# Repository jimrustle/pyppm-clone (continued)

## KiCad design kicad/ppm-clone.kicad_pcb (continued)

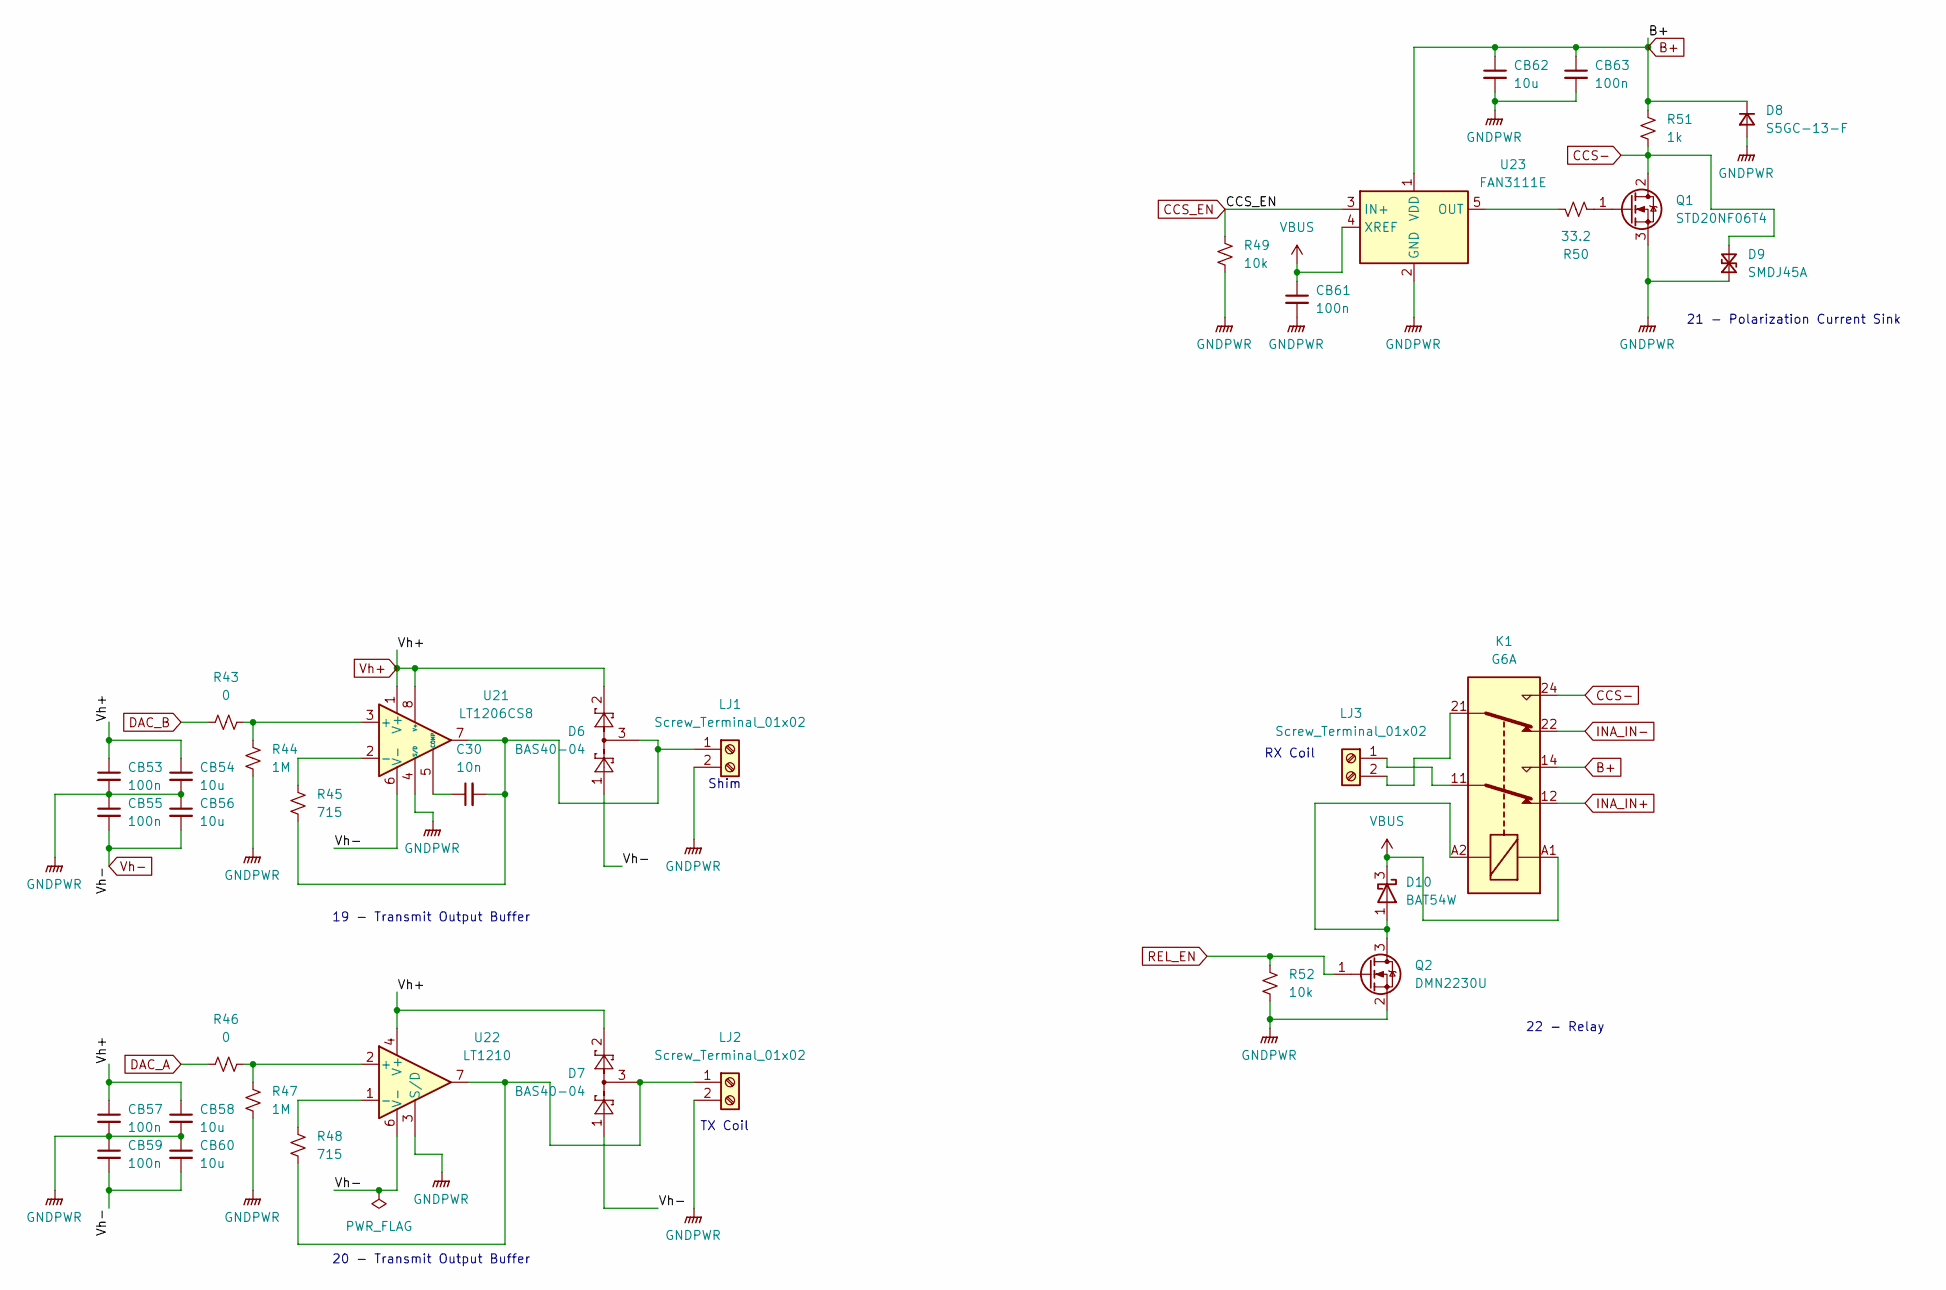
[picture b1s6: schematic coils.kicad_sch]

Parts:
C30: 10n; C_0603_1608Metric_Pad1.08x0.95mm_HandSolder
CB53, CB55, CB57, CB59, CB61, CB63: 100n; C_0603_1608Metric_Pad1.08x0.95mm_HandSolder
CB54, CB56, CB58, CB60, CB62: 10u; C_0603_1608Metric_Pad1.08x0.95mm_HandSolder
D6, D7: BAS40-04; SOT-23
D8: S5GC-13-F; D_SMC-RM10_Universal_Handsoldering
D9: SMDJ45A; D_SMC-RM10_Universal_Handsoldering
D10: BAT54W; SOT-323_SC-70
K1: G6A; Relay_DPDT_Omron_G6A
LJ1, LJ2, LJ3: Screw_Terminal_01x02; TerminalBlock_bornier-2_P5.08mm
Q1: STD20NF06T4; TO-252-2
Q2: DMN2230U; SOT-23
R43, R46: 0; R_0603_1608Metric_Pad0.98x0.95mm_HandSolder
R44, R47: 1M; R_0603_1608Metric_Pad0.98x0.95mm_HandSolder
R45, R48: 715; R_0603_1608Metric_Pad0.98x0.95mm_HandSolder
R49, R52: 10k; R_0603_1608Metric_Pad0.98x0.95mm_HandSolder
R50: 33.2; R_0603_1608Metric_Pad0.98x0.95mm_HandSolder
R51: 1k; R_0603_1608Metric_Pad0.98x0.95mm_HandSolder
U21: LT1206CS8; SO-8_3.9x4.9mm_P1.27mm
U22: LT1210; TO-263-7_TabPin4
U23: FAN3111E; SOT-23-5

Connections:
B+: CB62.1, CB63.1, D8.1 (K), K1.14, R51.1, U23.1 (VDD); also elsewhere on the board
CCS-: D9.2 (A2), K1.24, Q1.2 (D), R51.2
CCS_EN: R49.1, U23.3 (IN+); also elsewhere on the board
DAC_A: R46.1; also elsewhere on the board
DAC_B: R43.1; also elsewhere on the board
GNDPWR: CB53.2, CB54.2, CB55.1, CB56.1, CB57.2, CB58.2, CB59.1, CB60.1, CB61.2, CB62.2, CB63.2, D8.2 (A), D9.1 (A1), LJ1.2, LJ2.2, Q1.3 (S), Q2.2 (S), R44.2, R47.2, R49.2, R52.2, U21.4 (S/D), U22.3 (S/D), U23.2 (GND); also elsewhere on the board
INA_IN+: K1.12; also elsewhere on the board
INA_IN-: K1.22; also elsewhere on the board
unnamed: D10.1 (A), K1.A2, Q2.3 (D)
unnamed: C30.2, D6.3, LJ1.1, R45.2, U21.7
unnamed: D7.3, LJ2.1, R48.2, U22.7
unnamed: K1.11, LJ3.1
unnamed: K1.21, LJ3.2
unnamed: Q1.1 (G), R50.2
unnamed: R43.2, R44.1, U21.3 (+)
unnamed: R45.1, U21.2 (-)
unnamed: C30.1, U21.5 (COMP)
unnamed: R46.2, R47.1, U22.2 (+)
unnamed: R48.1, U22.1 (-)
unnamed: R50.1, U23.5 (OUT)
REL_EN: Q2.1 (G), R52.1; also elsewhere on the board
VBUS: CB61.1, D10.3 (K), K1.A1, U23.4 (XREF); also elsewhere on the board
Vh+: CB53.1, CB54.1, CB57.1, CB58.1, D6.2, D7.2, U21.1 (V+), U21.8 (V+), U22.4 (V+); also elsewhere on the board
Vh-: CB55.2, CB56.2, CB59.2, CB60.2, D6.1, D7.1, U21.6 (V-), U22.6 (V-); also elsewhere on the board

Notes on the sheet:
22 - Relay
Shim
19 - Transmit Output Buffer
21 - Polarization Current Sink
RX Coil
TX Coil
20 - Transmit Output Buffer

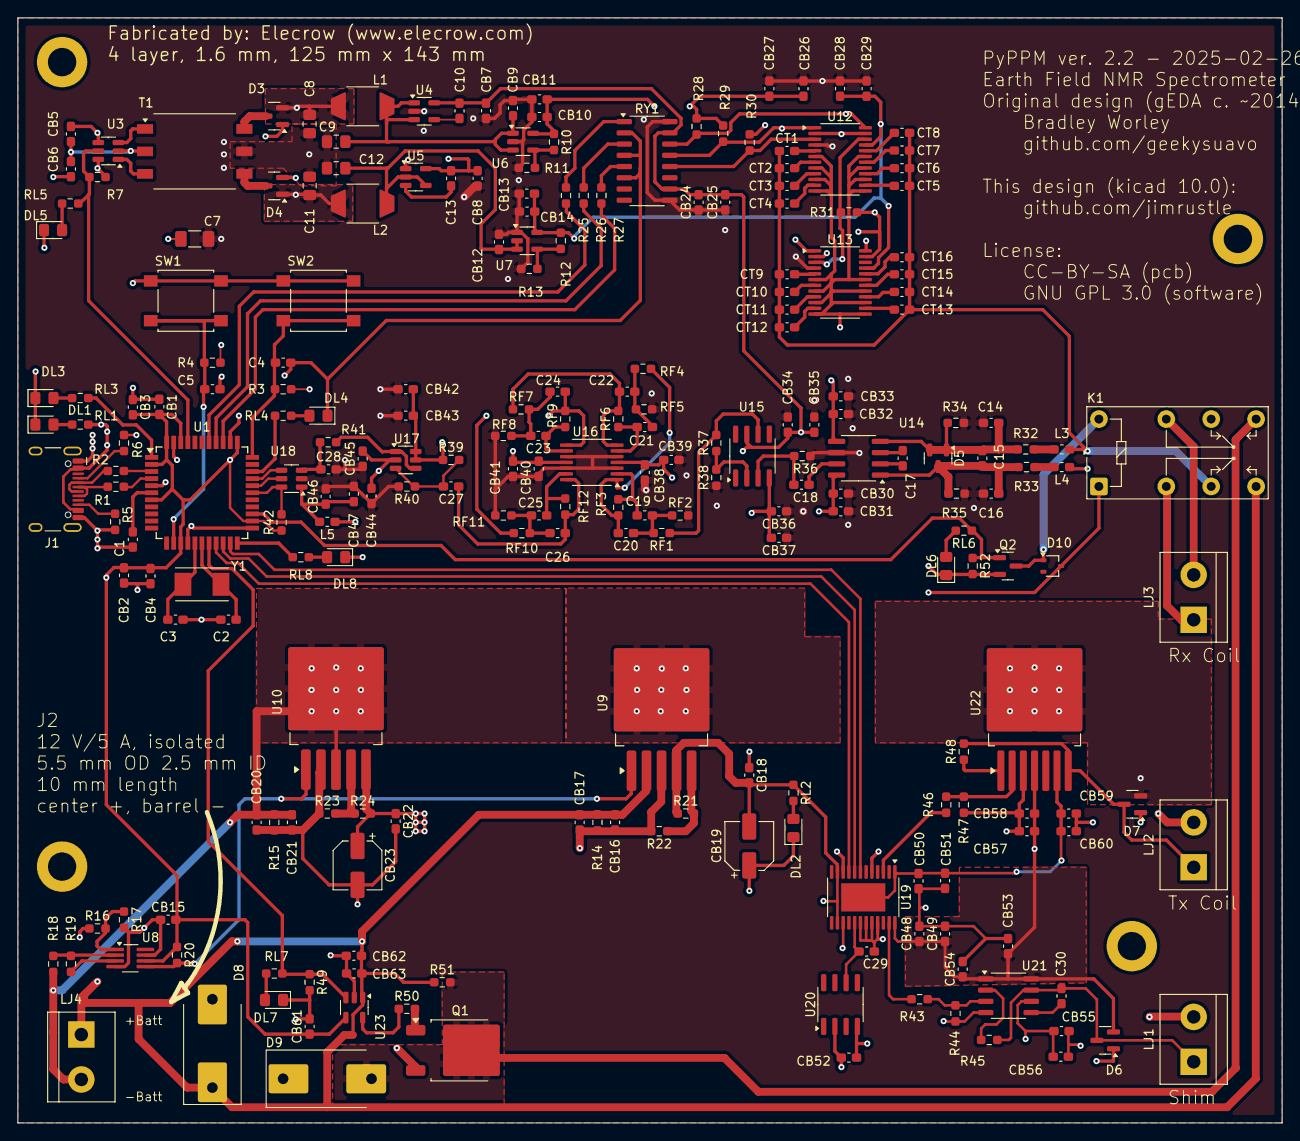
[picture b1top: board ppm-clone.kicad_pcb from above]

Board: 4 copper layers, 143.0 x 125.0 mm, 237 parts (0 on the bottom side), 130 nets.

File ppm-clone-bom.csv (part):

Reference,Value,Footprint,Qty,LCSC P/N,Notes,Check,Digikey PN,LCSC qty
"C1,C29,CB52,CT14",1u,Capacitor_SMD:C_0603_1608Metric_Pad1.08x0.95mm_HandSolder,4,C5673 ,25 V  X5R,x,490-5307-1-ND,50
"C2,C3",27p,Capacitor_SMD:C_0603_1608Metric_Pad1.08x0.95mm_HandSolder,2,C107045 ,,x,490-1413-1-ND,
"C4,C5,C15,C18,C27,CB1,CB2,CB9,CB10,CB12,CB13,CB15,CB16,CB18,CB20,CB22,CB24,CB26,CB28,CB30,CB32,CB34,CB36,CB38,CB40,CB42,CB44,CB46,CB48,CB50,CB53,CB55,CB57,CB59,CB61,CB63,CT10",100n,Capacitor_SMD:C_0603_1608Metric_Pad1.08x0.95mm_HandSolder,37,C14663 ,,x,490-1532-1-ND,
C7,2.2n / 1kV,Capacitor_SMD:C_1206_3216Metric_Pad1.33x1.80mm_HandSolder,1,C9191 ,,x,478-2953-1-ND,
"C8,C9,C11,C12",15u,Capacitor_SMD:C_0805_2012Metric_Pad1.18x1.45mm_HandSolder,4,,,,445-3927-1-ND,
"C10,C13,C14,C16,C19,C20,C21,C22,C23,C24,C25,C26,C28,C30",10n,Capacitor_SMD:C_0603_1608Metric_Pad1.08x0.95mm_HandSolder,14,C115056,,x,445-2664-1-ND,
C17,220p,Capacitor_SMD:C_0603_1608Metric_Pad1.08x0.95mm_HandSolder,1,C302060,film to mlcc,x,PCF1445CT-ND,
"CB3,CB4,CB7,CB8,CB11,CB14,CB17,CB21,CB25,CB27,CB29,CB31,CB33,CB35,CB37,CB39,CB41,CB43,CB45,CB47,CB49,CB51,CB54,CB56,CB58,CB60,CB62",10u,Capacitor_SMD:C_0603_1608Metric_Pad1.08x0.95mm_HandSolder,27,C96446 ,tantalum to mlcc,x,511-1683-1-ND,
"CB5,CB6,CT16",4.7u,Capacitor_SMD:C_0603_1608Metric_Pad1.08x0.95mm_HandSolder,3,C19666 ,,x,490-7199-1-ND,
"CB19,CB23",100u,Capacitor_SMD:CP_Elec_5x5.3,2,C134722 ,tant poly to alum,x,P16641CT-ND,
CT1,150p,Capacitor_SMD:C_0603_1608Metric_Pad1.08x0.95mm_HandSolder,1,C107038 ,film to mlcc,x,PCF1461CT-ND,
CT2,330p,Capacitor_SMD:C_0603_1608Metric_Pad1.08x0.95mm_HandSolder,1,C1664 ,film to mlcc,x,PCF1465CT-ND,
CT3,680p,Capacitor_SMD:C_0603_1608Metric_Pad1.08x0.95mm_HandSolder,1,C107055 ,film to mlcc,x,PCF1451CT-ND,
CT4,1.5n,Capacitor_SMD:C_0603_1608Metric_Pad1.08x0.95mm_HandSolder,1,C576797,film to mlcc,x,PCF1455CT-ND,
CT5,3.3n,Capacitor_SMD:C_0603_1608Metric_Pad1.08x0.95mm_HandSolder,1,C3877267,film to mlcc,x,PCF1171CT-ND,
CT6,6.8n,Capacitor_SMD:C_0603_1608Metric_Pad1.08x0.95mm_HandSolder,1,C307492 ,film to mlcc,x,PCF1175CT-ND,
CT7,15n,Capacitor_SMD:C_0603_1608Metric_Pad1.08x0.95mm_HandSolder,1,C2833636 ,film to mlcc,x,PCF1179CT-ND,
CT8,33n,Capacitor_SMD:C_0603_1608Metric_Pad1.08x0.95mm_HandSolder,1,C106856 ,film to mlcc,x,PCF1183CT-ND,
CT9,68n,Capacitor_SMD:C_0603_1608Metric_Pad1.08x0.95mm_HandSolder,1,C107098 ,film to mlcc,x,PCF1187CT-ND,
CT11,220n,Capacitor_SMD:C_0603_1608Metric_Pad1.08x0.95mm_HandSolder,1,C344195 ,film to mlcc,x,PCF1128CT-ND,
CT12,330n,Capacitor_SMD:C_0603_1608Metric_Pad1.08x0.95mm_HandSolder,1,C282682 ,film to mlcc,x,PCF1129CT-ND,
CT13,680n,Capacitor_SMD:C_0603_1608Metric_Pad1.08x0.95mm_HandSolder,1,C5143539 ,film to mlcc,x,PCF1131CT-ND,
CT15,2.2u,Capacitor_SMD:C_0603_1608Metric_Pad1.08x0.95mm_HandSolder,1,C5184421,,x,490-3296-1-ND,
"D3,D4,D6,D7",BAS40-04,Package_TO_SOT_SMD:SOT-23,4,C40919 ,,x,BAS40-04-V-GS08CT-ND,
D5,BAV199,Package_TO_SOT_SMD:SOT-23,1,C40919 ,bav199,x,568-1619-1-ND,
D8,S5GC-13-F,Diode_SMD:D_SMC-RM10_Universal_Handsoldering,1,C211400 ,,x,S5GC-FDICT-ND,
D9,SMDJ45A,Diode_SMD:D_SMC-RM10_Universal_Handsoldering,1,C4154731 ,,x,SMDJ45ACT-ND,
D10,BAT54W,Package_TO_SOT_SMD:SOT-323_SC-70,1,C8657 ,slower,x,SD101AWSTPMSCT-ND,
"DL1,DL2,DL3,DL4,DL5,DL6,DL7,DL8",LED,LED_SMD:LED_0805_2012Metric_Pad1.15x1.40mm_HandSolder,8,C22371297,"10 mA, 0603",x,160-1828-1-ND,
J1,USB_C_Receptacle_USB2.0_14P,Connector_USB:USB_C_Receptacle_HCTL_HC-TYPE-C-16P-01A,1,C2894897,,x,,
J2,Barrel_Jack,,1,,,x,,
K1,G6A,Relay_THT:Relay_DPDT_Omron_G6A,1,C146834 ,,x,Z123-ND,
"L1,L2",33u,ppm-clone:SDR6603,2,,OUT OF STOCK,,,
"L3,L4,L5",BLM18PG121SN1D,Inductor_SMD:L_0603_1608Metric_Pad1.05x0.95mm_HandSolder,3,C14709 ,,x,490-1037-1-ND,
"LJ1,LJ2,LJ3",Screw_Terminal_01x02,TerminalBlock_TE-Connectivity:TerminalBlock_TE_282834-2_1x02_P2.54mm_Horizontal,3,C8465,,x,,
Q1,STD20NF06T4,Package_TO_SOT_SMD:TO-252-2,1,C22366765 ,,x,IRLR024NPBFCT-ND,
Q2,DMN2230U,Package_TO_SOT_SMD:SOT-23,1,C516590 ,RDS worse,,FDN327NCT-ND,
"R1,R2",22,Resistor_SMD:R_0603_1608Metric_Pad0.98x0.95mm_HandSolder,2,C23345 ,,,P22.0HCT-ND,
"R3,R4,R7,R20,R28,R29,R30,R31,R39,R40,R42,R49,R52",10k,Resistor_SMD:R_0603_1608Metric_Pad0.98x0.95mm_HandSolder,13,C2930027 ,,,P10.0KHCT-ND,
"R5,R6",5.1k,Resistor_SMD:R_0603_1608Metric_Pad0.98x0.95mm_HandSolder,2,C2907114 ,,,,
"R10,R12",1.05k,Resistor_SMD:R_0603_1608Metric_Pad0.98x0.95mm_HandSolder,2,C2930047 ,,,P1.05KHCT-ND,
"R11,R13,R22,R23,R37,R51",1k,Resistor_SMD:R_0603_1608Metric_Pad0.98x0.95mm_HandSolder,6,C2907113 ,,,P1.00KHCT-ND,
"R14,R15,R17,R19,R36",100k,Resistor_SMD:R_0603_1608Metric_Pad0.98x0.95mm_HandSolder,5,C14675 ,,,P100KHCT-ND,
R16,1.3M,Resistor_SMD:R_0603_1608Metric_Pad0.98x0.95mm_HandSolder,1,C2974026 ,,,P1.3MGCT-ND,
R18,1.5M,Resistor_SMD:R_0603_1608Metric_Pad0.98x0.95mm_HandSolder,1,C4172 ,,,P1.5MGCT-ND,
"R21,R24",3.16k,Resistor_SMD:R_0603_1608Metric_Pad0.98x0.95mm_HandSolder,2,C2930087 ,,,P3.16KHCT-ND,
"R25,R26,R27",330,Resistor_SMD:R_0603_1608Metric_Pad0.98x0.95mm_HandSolder,3,C23138 ,,,P330HCT-ND,
"R32,R33,R41",49.9,Resistor_SMD:R_0603_1608Metric_Pad0.98x0.95mm_HandSolder,3,C2930110 ,,,P49.9DBCT-ND,
"R34,R35,R44,R47",1M,Resistor_SMD:R_0603_1608Metric_Pad0.98x0.95mm_HandSolder,4,C22935 ,,,A102234CT-ND,
R38,10,Resistor_SMD:R_0603_1608Metric_Pad0.98x0.95mm_HandSolder,1,C22859 ,,,CRT0603-BY-10R0ELFCT-ND,
"R43,R46",0,Resistor_SMD:R_0603_1608Metric_Pad0.98x0.95mm_HandSolder,2,C21189 ,,,P0.0GCT-ND,
"R45,R48",715,Resistor_SMD:R_0603_1608Metric_Pad0.98x0.95mm_HandSolder,2,C2998136 ,,,P715DBCT-ND,
R50,33.2,Resistor_SMD:R_0603_1608Metric_Pad0.98x0.95mm_HandSolder,1,C2930093 ,,,P33.2HCT-ND,
RF1,14.3k,Resistor_SMD:R_0603_1608Metric_Pad0.98x0.95mm_HandSolder,1,C2933145 ,,,P14.3KHCT-ND,
RF2,15.4k,Resistor_SMD:R_0603_1608Metric_Pad0.98x0.95mm_HandSolder,1,C2933150 ,,,P15.4KHCT-ND,
RF3,45.3k,Resistor_SMD:R_0603_1608Metric_Pad0.98x0.95mm_HandSolder,1,C2933224 ,,,P45.3KHCT-ND,
RF4,5.49k,Resistor_SMD:R_0603_1608Metric_Pad0.98x0.95mm_HandSolder,1,C3000723 ,,,P5.49KHCT-ND,
RF5,6.04k,Resistor_SMD:R_0603_1608Metric_Pad0.98x0.95mm_HandSolder,1,C25977 ,,,P6.04KHCT-ND,
RF6,17.4k,Resistor_SMD:R_0603_1608Metric_Pad0.98x0.95mm_HandSolder,1,C2930069 ,,,P17.4KHCT-ND,
RF7,13.3k,Resistor_SMD:R_0603_1608Metric_Pad0.98x0.95mm_HandSolder,1,C2933140 ,,,P13.3KHCT-ND,
RF8,5.23k,Resistor_SMD:R_0603_1608Metric_Pad0.98x0.95mm_HandSolder,1,C2930111 ,,,P5.23KHCT-ND,
RF9,232k,Resistor_SMD:R_0603_1608Metric_Pad0.98x0.95mm_HandSolder,1,C2998117 ,,,P232KHCT-ND,
RF10,2k,Resistor_SMD:R_0603_1608Metric_Pad0.98x0.95mm_HandSolder,1,C2907137 ,,,P2.00KHCT-ND,
RF11,732,Resistor_SMD:R_0603_1608Metric_Pad0.98x0.95mm_HandSolder,1,C245063 ,,,P732HCT-ND,
RF12,34.8k,Resistor_SMD:R_0603_1608Metric_Pad0.98x0.95mm_HandSolder,1,C23141 ,,,P34.8KHCT-ND,
"RL1,RL2,RL3,RL4,RL5,RL6,RL7,RL8",100,Resistor_SMD:R_0603_1608Metric_Pad0.98x0.95mm_HandSolder,8,,500 ohm,,P604HCT-ND,
RY1,ACSL-6300,Package_SO:SO-16_3.9x9.9mm_P1.27mm,1,C6800668 ,,,516-2221-1-ND,
"SW1,SW2",SW_Push,Button_Switch_SMD:SW_SPST_B3S-1000,2,,OUT OF STOCK,,,
T1,78931812512,Transformer_SMD:Transformer_Wuerth_750315371,1,,OUT OF STOCK,,,
U1,ATmega32U4-A,Package_QFP:TQFP-44_10x10mm_P0.8mm,1,C2052746 ,,,ATMEGA32U4-AU-ND,3
U3,SN6505BDBV,Package_TO_SOT_SMD:SOT-23-6,1,C2156022 ,,,LT3439EFE#PBF-ND,3
U4,LT1761-5,Package_TO_SOT_SMD:TSOT-23-5,1,C655160 ,,,LT1761ES5-5#TRMPBFCT-ND,3
U5,LT1964-5,Package_TO_SOT_SMD:TSOT-23-5,1,C5357091 ,,,LT1964ES5-5#TRMPBFCT-ND,3
U6,LT1761-SD,Package_TO_SOT_SMD:TSOT-23-5,1,C117432 ,,,LT1761ES5-SD#TRMPBFCT-ND,3
U7,LT1964-SD,Package_TO_SOT_SMD:TSOT-23-5,1,C117431 ,,,LT1964ES5-SD#TRMPBFCT-ND,3
U8,LTC2909,Package_TO_SOT_SMD:TSOT-23-8_HandSoldering,1,,OUT OF STOCK,,LTC2909CTS8-5#TRMPBFCT-ND,
U9,LT1764AEQ,Package_TO_SOT_SMD:TO-263-5_TabPin3,1,C459712 ,,,LT1764AEQ#TRPBFCT-ND,3
U10,LT3015xQ-5,Package_TO_SOT_SMD:TO-263-5_TabPin3,1,C666317 ,,,LT3015EQ#PBF-ND,3
"U12,U13",ADG714,Package_SO:TSSOP-24_4.4x7.8mm_P0.65mm,2,C462201 ,,,ADG714BRUZ-REEL7CT-ND,3
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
